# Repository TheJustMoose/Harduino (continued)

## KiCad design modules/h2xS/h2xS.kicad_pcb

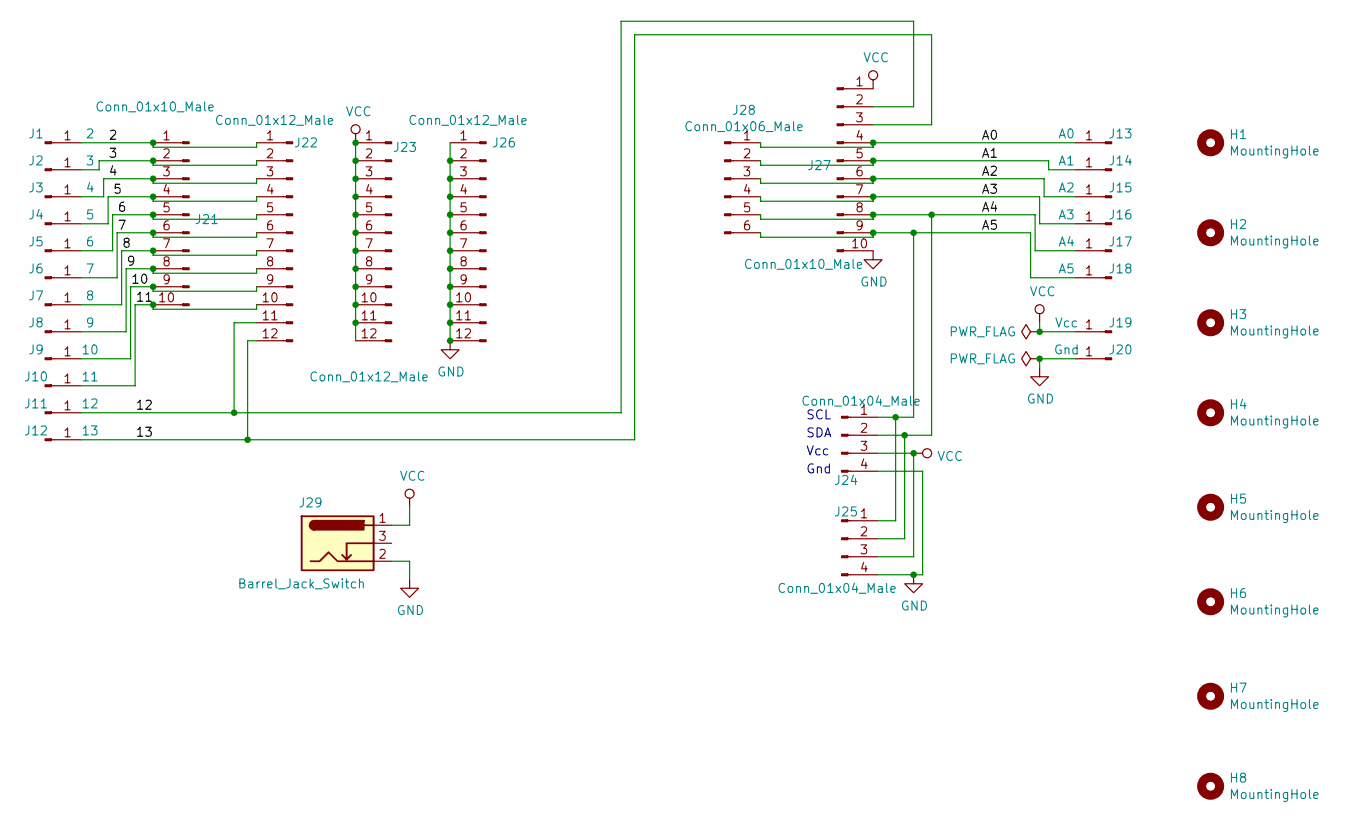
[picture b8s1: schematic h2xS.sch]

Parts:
H1, H2, H3, H4, H5, H6, H7, H8: MountingHole; MountingHole_3.2mm_M3
J1: 2; PinHeader_1x01_P2.54mm_Vertical
J2: 3; PinHeader_1x01_P2.54mm_Vertical
J3: 4; PinHeader_1x01_P2.54mm_Vertical
J4: 5; PinHeader_1x01_P2.54mm_Vertical
J5: 6; PinHeader_1x01_P2.54mm_Vertical
J6: 7; PinHeader_1x01_P2.54mm_Vertical
J7: 8; PinHeader_1x01_P2.54mm_Vertical
J8: 9; PinHeader_1x01_P2.54mm_Vertical
J9: 10; PinHeader_1x01_P2.54mm_Vertical
J10: 11; PinHeader_1x01_P2.54mm_Vertical
J11: 12; PinHeader_1x01_P2.54mm_Vertical
J12: 13; PinHeader_1x01_P2.54mm_Vertical
J13: A0; PinHeader_1x01_P2.54mm_Vertical
J14: A1; PinHeader_1x01_P2.54mm_Vertical
J15: A2; PinHeader_1x01_P2.54mm_Vertical
J16: A3; PinHeader_1x01_P2.54mm_Vertical
J17: A4; PinHeader_1x01_P2.54mm_Vertical
J18: A5; PinHeader_1x01_P2.54mm_Vertical
J19: Vcc; PinHeader_1x01_P2.54mm_Vertical
J20: Gnd; PinHeader_1x01_P2.54mm_Vertical
J21, J27: Conn_01x10_Male; PinSocket_1x10_P2.54mm_Vertical
J22, J23, J26: Conn_01x12_Male; PinHeader_1x12_P2.54mm_Vertical
J24, J25: Conn_01x04_Male; PinHeader_1x04_P2.54mm_Vertical
J28: Conn_01x06_Male; PinHeader_1x06_P2.54mm_Vertical
J29: Barrel_Jack_Switch; BarrelJack_Horizontal

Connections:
/2: J1.1, J21.1, J22.1
/3: J2.1, J21.2, J22.2
/4: J3.1, J21.3, J22.3
/5: J4.1, J21.4, J22.4
/6: J5.1, J21.5, J22.5
/7: J6.1, J21.6, J22.6
/8: J7.1, J21.7, J22.7
/9: J8.1, J21.8, J22.8
/10: J9.1, J21.9, J22.9
/11: J10.1, J21.10, J22.10
/12: J11.1, J22.11, J27.2
/13: J12.1, J22.12, J27.3
/A0: J13.1, J27.4, J28.1
/A1: J14.1, J27.5, J28.2
/A2: J15.1, J27.6, J28.3
/A3: J16.1, J27.7, J28.4
/A4: J17.1, J24.2, J25.2, J27.8, J28.5
/A5: J18.1, J24.1, J25.1, J27.9, J28.6
GND: J20.1, J24.4, J25.4, J26.1, J26.2, J26.3, J26.4, J26.5, J26.6, J26.7, J26.8, J26.9, J26.10, J26.11, J26.12, J27.10, J29.2
VCC: J19.1, J23.1, J23.2, J23.3, J23.4, J23.5, J23.6, J23.7, J23.8, J23.9, J23.10, J23.11, J23.12, J24.3, J25.3, J27.1, J29.1

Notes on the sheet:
Gnd
Vcc
SDA
SCL

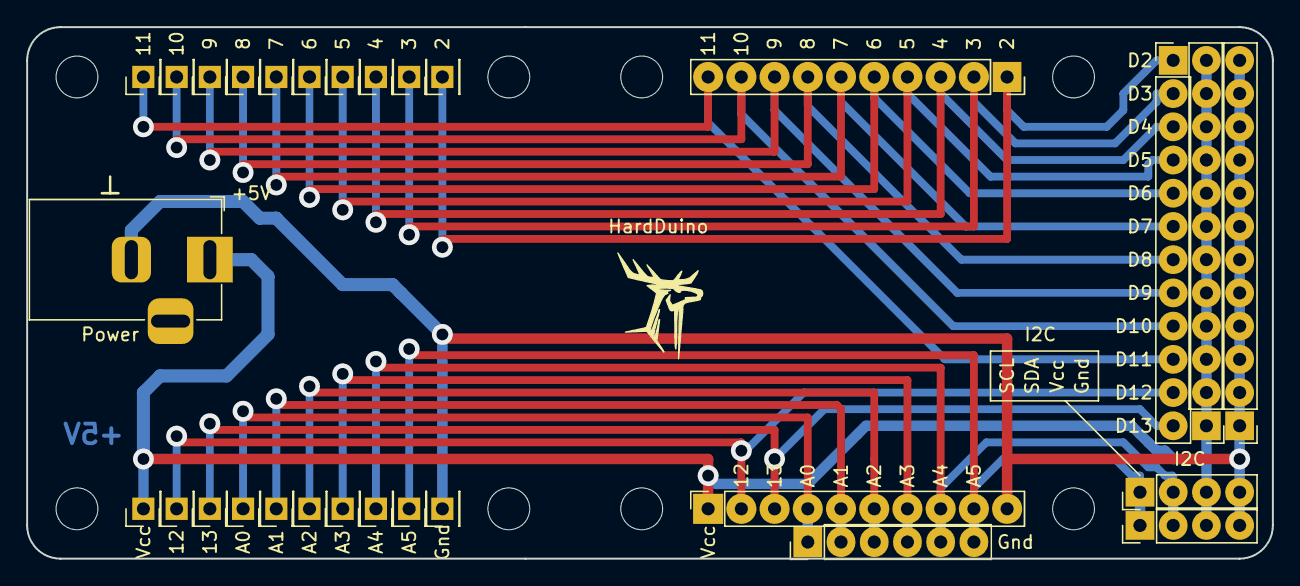
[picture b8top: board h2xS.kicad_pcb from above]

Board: 2 copper layers, 95.2 x 40.6 mm, 37 parts (0 on the bottom side), 20 nets.
